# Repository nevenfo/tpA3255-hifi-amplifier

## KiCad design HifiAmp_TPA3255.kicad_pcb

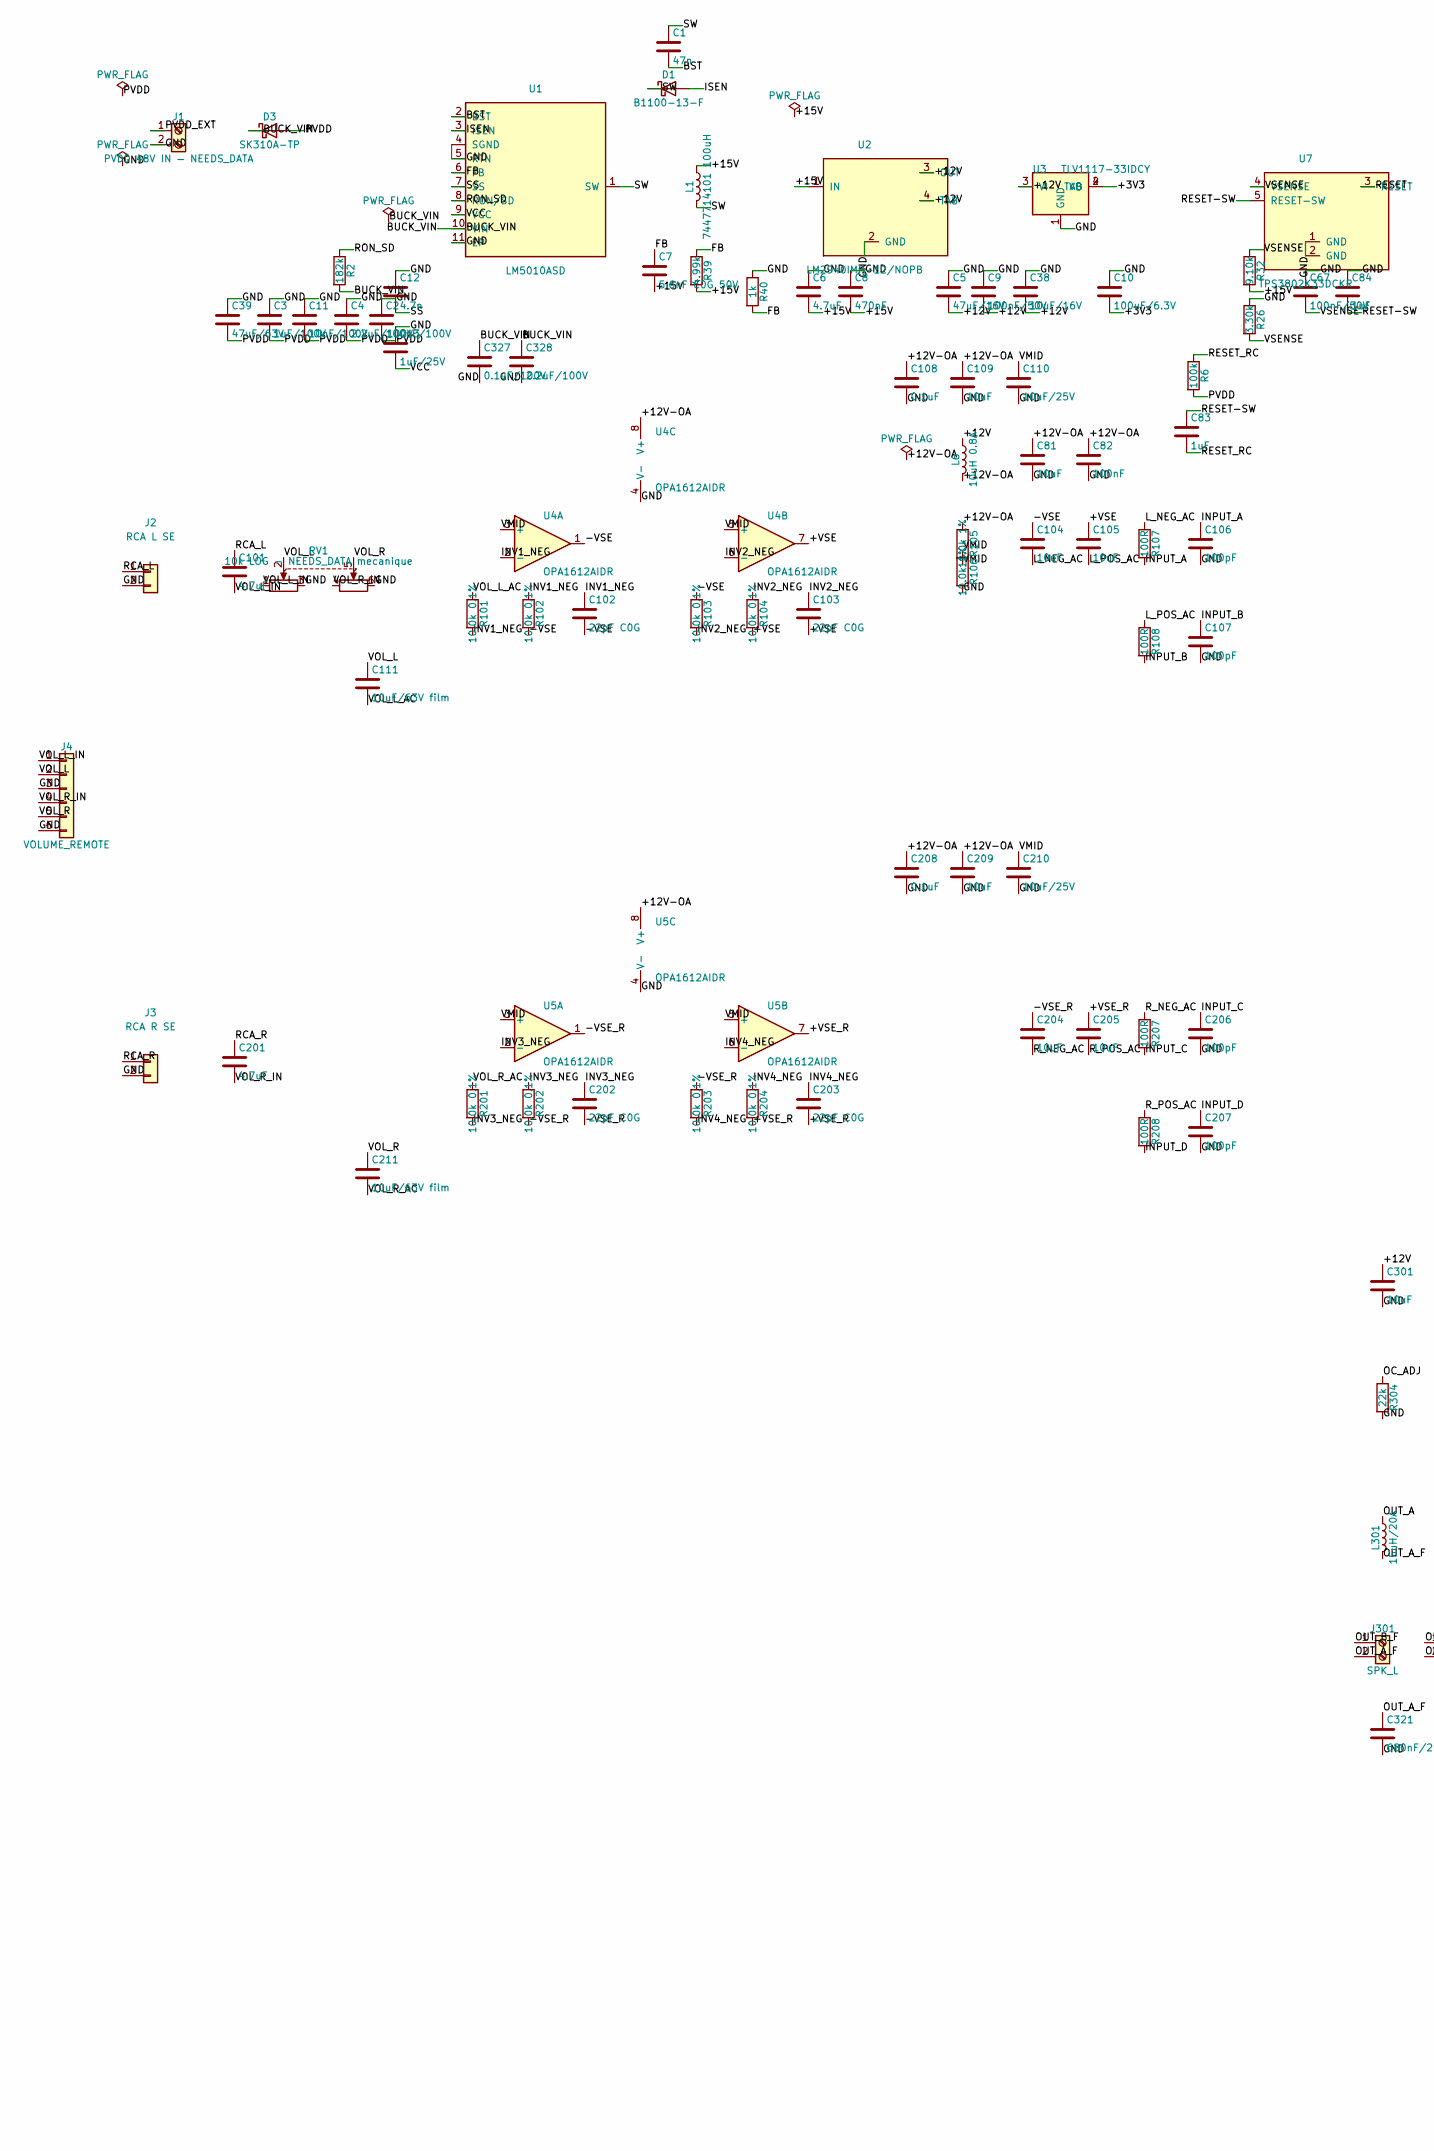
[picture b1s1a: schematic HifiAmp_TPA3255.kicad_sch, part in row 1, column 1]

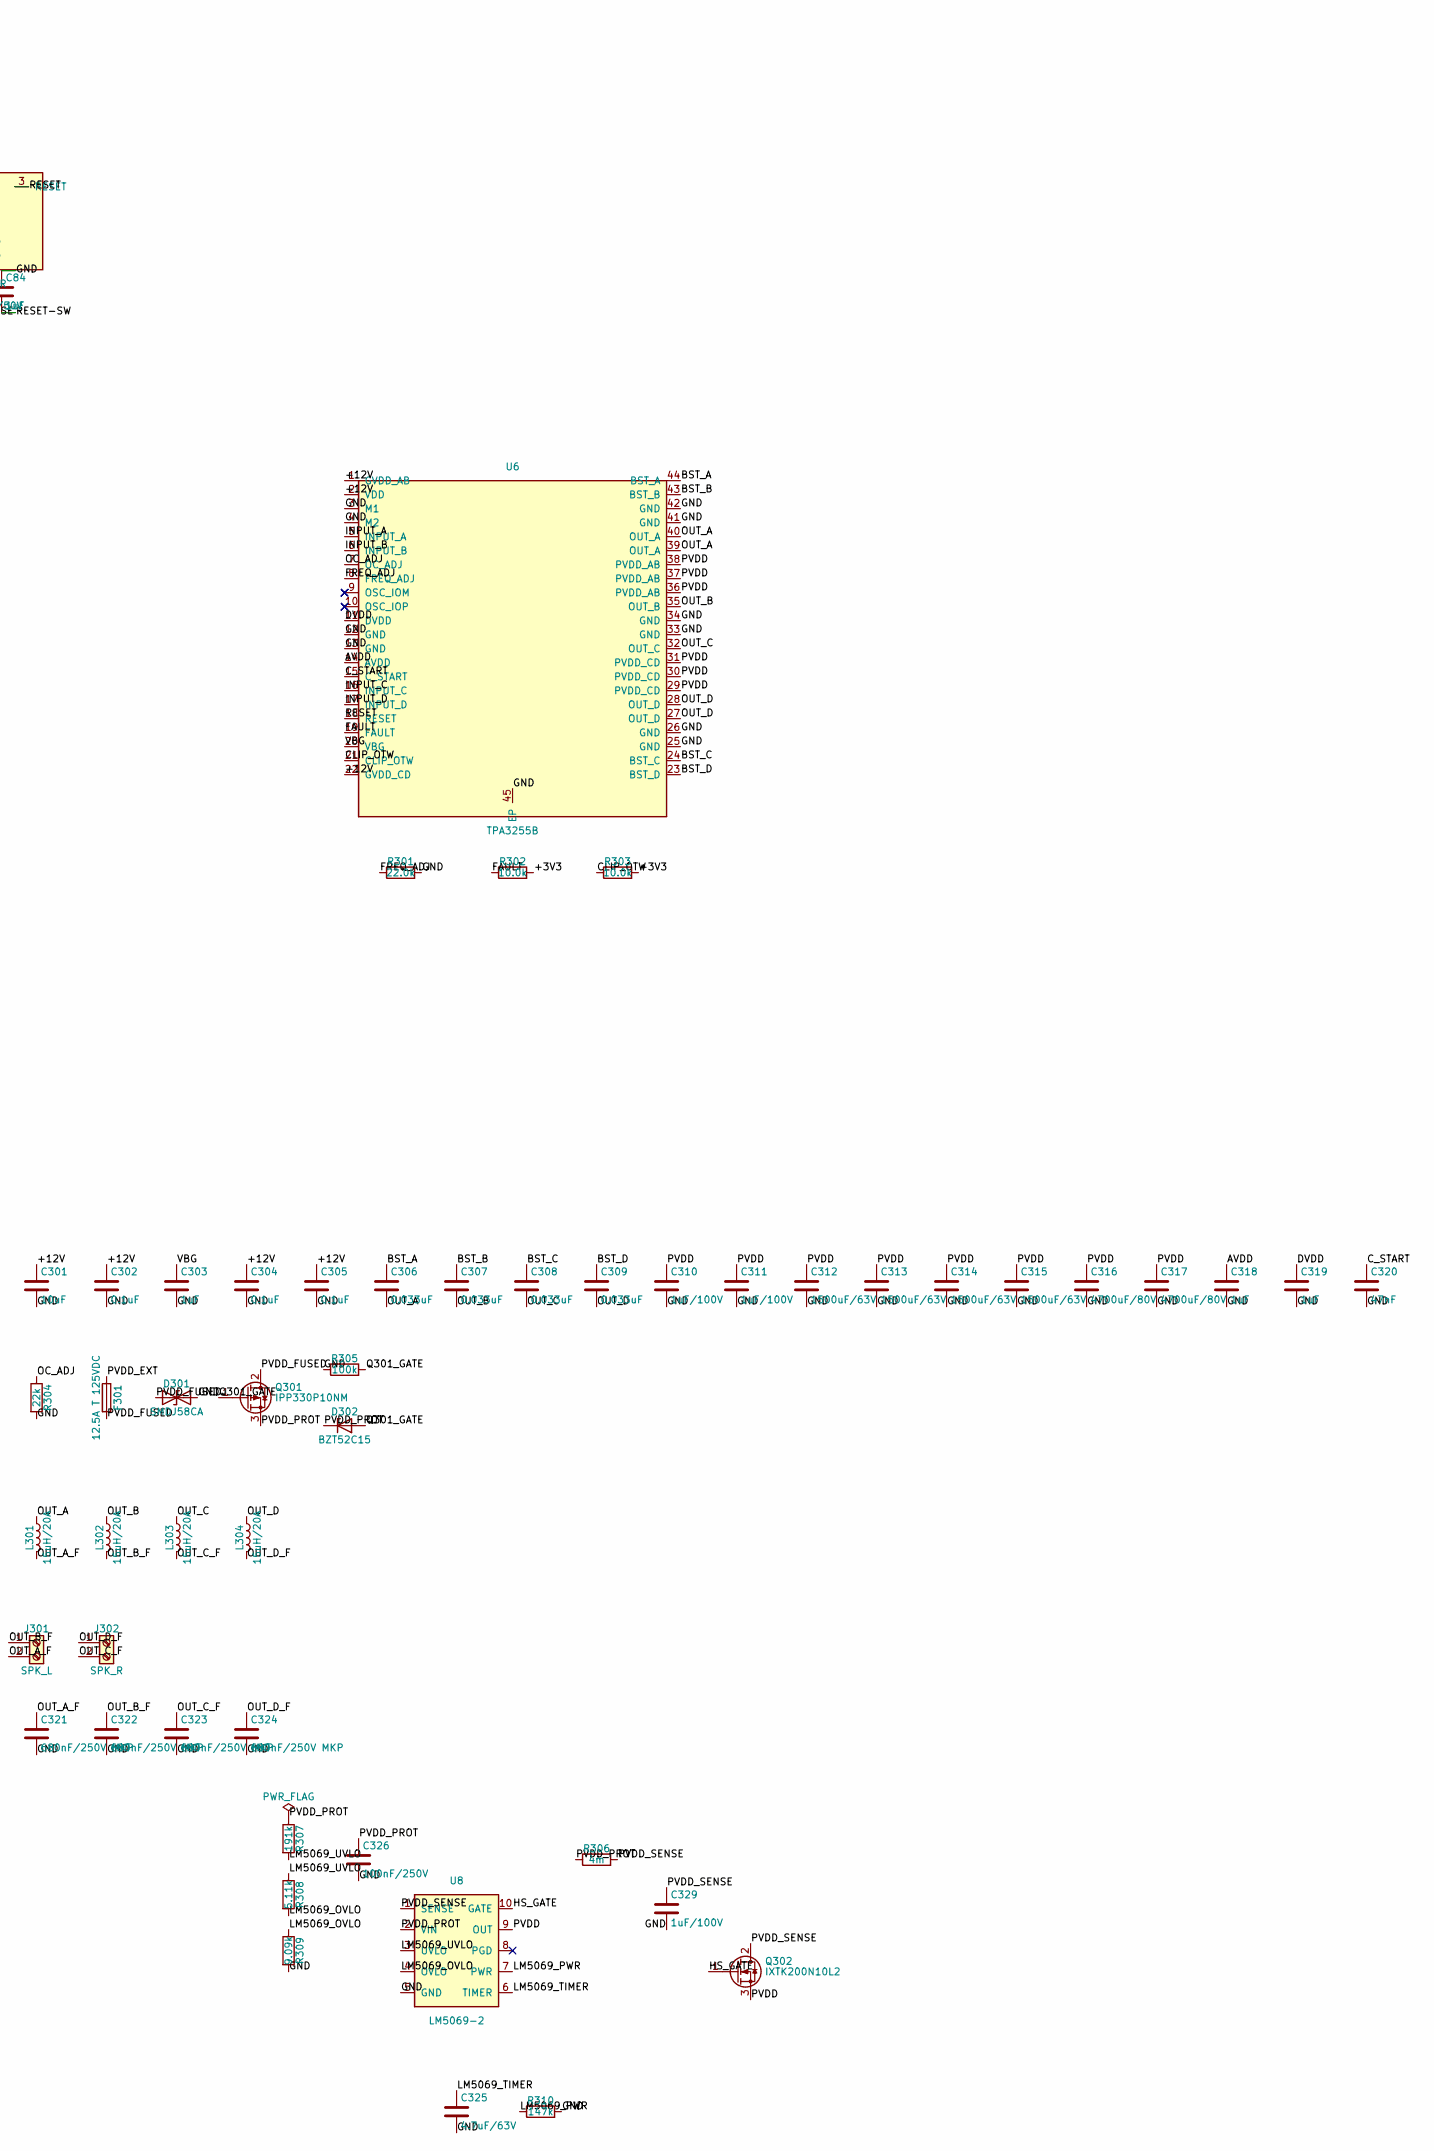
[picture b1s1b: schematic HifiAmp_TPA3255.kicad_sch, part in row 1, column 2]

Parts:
C1: 47n; C_0603_1608Metric
C2: 100nF/100V; C_1206_3216Metric
C3, C310, C311, C329: 1uF/100V; C_1210_3225Metric
C4: 2.2uF/100V; C_1812_4532Metric
C5: 47uF/16V; C_1210_3225Metric
C6, C101, C201: 4.7uF; C_0805_2012Metric
C7: 5.6nF C0G 50V; C_0603_1608Metric
C8: 470nF; C_0805_2012Metric
C9, C67: 100nF/50V; C_0805_2012Metric
C10: 100uF/6.3V; C_1210_3225Metric
C11: 10nF/100V; C_0805_2012Metric
C12: 4.7n; C_0603_1608Metric
C13: 1uF/25V; C_0603_1608Metric
C38: 10uF/16V; C_0805_2012Metric
C39: 47uF/63V; CP_Radial_D8.0mm_P3.50mm
C81, C104, C105, C109, C204, C205, C209, C301: 10uF; C_0805_2012Metric
C82: 100nF; C_0805_2012Metric
C83, C84, C303, C318, C319: 1uF; C_0805_2012Metric
C102, C103, C202, C203: 22pF C0G; C_0603_1608Metric
C106, C107, C206, C207: 100pF; C_0603_1608Metric
C108, C208, C302, C304, C305: 0.1uF; C_0603_1608Metric
C110, C210: 10uF/25V; C_0805_2012Metric
C111, C211: 10uF/63V film; C_Rect_L26.5mm_W10.5mm_P22.50mm_MKS4
C306, C307, C308, C309: 0.033uF; C_0603_1608Metric
C312, C313, C314, C315: 1500uF/63V; CP_Radial_D18.0mm_P7.50mm
C316, C317: 4700uF/80V; CP_Radial_D35.0mm_P10.00mm_SnapIn
C320: 47nF; C_0603_1608Metric
C321, C322, C323, C324: 680nF/250V MKP; C_Rect_L18.0mm_W8.0mm_P15.00mm_FKS3_FKP3
C325: 4.7uF/63V; C_Rect_L7.2mm_W11.0mm_P5.00mm_FKS2_FKP2_MKS2_MKP2; MPN MKS2C044701O00KSSD
C326: 100nF/250V; C_1206_3216Metric
C327: 0.1uF/100V; C_0603_1608Metric
C328: 2.2uF/100V; C_1210_3225Metric
D1: B1100-13-F; D_SMA
D3: SK310A-TP; D_SMA
D301: SMDJ58CA; D_SMC; MPN SMDJ58CA
D302: BZT52C15; D_SOD-123; MPN BZT52C15
F301: 12.5A T 125VDC; Fuse_Schurter_UMT-H_5.3x16mm; MPN 3403.0285.11
J1: PVDD 48V IN — NEEDS_DATA; TerminalBlock_MaiXu_MX126-5.0-02P_1x02_P5.00mm
J2: RCA L SE; JST_XH_B2B-XH-A_1x02_P2.50mm_Vertical
J3: RCA R SE; JST_XH_B2B-XH-A_1x02_P2.50mm_Vertical
J4: VOLUME_REMOTE; JST_XH_B6B-XH-A_1x06_P2.50mm_Vertical
J301: SPK_L; TerminalBlock_MaiXu_MX126-5.0-02P_1x02_P5.00mm
J302: SPK_R; TerminalBlock_MaiXu_MX126-5.0-02P_1x02_P5.00mm
L1: 7447714101 100uH; L_Wuerth_WE-PD-1050_10x10x5mm
L6: 10uH 0.8A; L_Wuerth_WE-PD-Typ-M-Typ-S
L301, L302, L303, L304: 15uH/20A; L_Toroid_Vertical_L28.6mm_W12.3mm_P10.00mm_Coilcraft_PA6331
Q301: IPP330P10NM; TO-220-3_Vertical; MPN IPP330P10NM
Q302: IXTK200N10L2; TO-264-3_Vertical; MPN IXTK200N10L2
R2: 182k; R_0603_1608Metric
R6: 100k; R_0603_1608Metric
R26: 3.30k; R_0603_1608Metric
R32: 9.10k; R_0603_1608Metric
R39: 4.99k; R_0603_1608Metric
R40: 1k; R_0603_1608Metric
R101, R102, R103, R104, R201, R202, R203, R204: 10.0k 0.1%; R_0603_1608Metric
R105, R106: 10.0k 1%; R_0603_1608Metric
R107, R108, R207, R208: 100R; R_0805_2012Metric
R301: 22.0k; R_0603_1608Metric
R302, R303: 10.0k; R_0603_1608Metric
R304: 22k; R_0603_1608Metric
R305: 100k; R_0805_2012Metric
R306: 4m; R_2512_6332Metric; MPN WSL25124L000FEA
R307: 191k; R_0805_2012Metric
R308: 5.11k; R_0603_1608Metric
R309: 9.09k; R_0603_1608Metric
R310: 147k; R_0603_1608Metric
RV1: 10k LOG - NEEDS_DATA mecanique
U1: LM5010ASD; WSON-10-1EP_4x4mm_P0.8mm_EP2.6x3mm
U2: LM2940IMP-12/NOPB; SOT-223
U3: TLV1117-33IDCY; SOT-223
U4, U5: OPA1612AIDR; SOIC-8_3.9x4.9mm_P1.27mm
U6: TPA3255B; HTSSOP-44_6.1x14mm_P0.635mm_TopEP4.14x7.01mm
U7: TPS3802K33DCKR; SOT-353_SC-70-5
U8: LM5069-2; MSOP-10_3x3mm_P0.5mm

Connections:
/+3V3: C10.2, R302.2, R303.2, U3.2 (VO), U3.4 (TAB)
/+12V: C5.2, C9.2, C38.2, C301.1, C302.1, C304.1, C305.1, L6.1, U2.3 (OUT), U2.4 (TAB), U3.3 (VI), U6.1 (GVDD_AB), U6.2 (VDD), U6.22 (GVDD_CD)
/+12V-OA: C81.1, C82.1, C108.1, C109.1, C208.1, C209.1, L6.2, R105.1, U4.8 (V+), U5.8 (V+)
/+15V: C6.2, C7.2, C8.2, L1.1, R32.2, R39.2, U2.1 (IN)
/+VSE: C103.2, C105.1, R104.2, U4.7
/+VSE_R: C203.2, C205.1, R204.2, U5.7
/-VSE: C102.2, C104.1, R102.2, R103.1, U4.1
/-VSE_R: C202.2, C204.1, R202.2, R203.1, U5.1
/AVDD: C318.1, U6.14 (AVDD)
/BST: C1.2, U1.2 (BST)
/BST_A: C306.1, U6.44 (BST_A)
/BST_B: C307.1, U6.43 (BST_B)
/BST_C: C308.1, U6.24 (BST_C)
/BST_D: C309.1, U6.23 (BST_D)
/BUCK_VIN: C327.1, C328.1, D3.1 (K), R2.2, U1.10 (VIN)
/CLIP_OTW: R303.1, U6.21 (CLIP_OTW)
/C_START: C320.1, U6.15 (C_START)
/DVDD: C319.1, U6.11 (DVDD)
/FAULT: R302.1, U6.19 (FAULT)
/FB: C7.1, R39.1, R40.2, U1.6 (FB)
/FREQ_ADJ: R301.1, U6.8 (FREQ_ADJ)
/GND: C2.1, C3.1, C4.1, C5.1, C6.1, C8.1, C9.1, C10.1, C11.1, C12.1, C13.1, C38.1, C39.1, C67.1, C81.2, C82.2, C84.1, C106.2, C107.2, C108.2, C109.2, C110.2, C206.2, C207.2, C208.2, C209.2, C210.2, C301.2, C302.2, C303.2, C304.2, C305.2, C310.2, C311.2, C312.2, C313.2, C314.2, C315.2, C316.2, C317.2, C318.2, C319.2, C320.2, C321.2, C322.2, C323.2, C324.2, C325.2, C326.2, C327.2, C328.2, C329.2, D301.2 (A2), J1.2, J2.2, J3.2, J4.3, J4.6, R26.1, R40.1, R106.2, R301.2, R304.2, R305.1, R309.2, R310.2, RV1.3, RV1.6, U1.4 (SGND), U1.5 (RTN), U1.11 (EP), U2.2 (GND), U3.1 (GND), U4.4 (V-), U5.4 (V-), U6.3 (M1), U6.4 (M2), U6.12 (GND), U6.13 (GND), U6.25 (GND), U6.26 (GND), U6.33 (GND), U6.34 (GND), U6.41 (GND), U6.42 (GND), U6.45 (EP), U7.1 (GND), U7.2 (GND), U8.5 (GND); also elsewhere on the board
/HS_GATE: Q302.1 (G), U8.10 (GATE)
/INPUT_A: C106.1, R107.2, U6.5 (INPUT_A)
/INPUT_B: C107.1, R108.2, U6.6 (INPUT_B)
/INPUT_C: C206.1, R207.2, U6.16 (INPUT_C)
/INPUT_D: C207.1, R208.2, U6.17 (INPUT_D)
/INV1_NEG: C102.1, R101.2, R102.1, U4.2 (-)
/INV2_NEG: C103.1, R103.2, R104.1, U4.6 (-)
/INV3_NEG: C202.1, R201.2, R202.1, U5.2 (-)
/INV4_NEG: C203.1, R203.2, R204.1, U5.6 (-)
/ISEN: D1.2 (A), U1.3 (ISEN)
/LM5069_OVLO: R308.2, R309.1, U8.4 (OVLO)
/LM5069_PWR: R310.1, U8.7 (PWR)
/LM5069_TIMER: C325.1, U8.6 (TIMER)
/LM5069_UVLO: R307.2, R308.1, U8.3 (UVLO)
/L_NEG_AC: C104.2, R107.1
/L_POS_AC: C105.2, R108.1
/OC_ADJ: R304.1, U6.7 (OC_ADJ)
/OUT_A: C306.2, L301.1, U6.39 (OUT_A), U6.40 (OUT_A)
/OUT_A_F: C321.1, J301.2, L301.2; also elsewhere on the board
/OUT_B: C307.2, L302.1, U6.35 (OUT_B)
/OUT_B_F: C322.1, J301.1, L302.2; also elsewhere on the board
/OUT_C: C308.2, L303.1, U6.32 (OUT_C)
/OUT_C_F: C323.1, J302.2, L303.2; also elsewhere on the board
/OUT_D: C309.2, L304.1, U6.27 (OUT_D), U6.28 (OUT_D)
/OUT_D_F: C324.1, J302.1, L304.2; also elsewhere on the board
/PVDD: C2.2, C3.2, C4.2, C11.2, C39.2, C310.1, C311.1, C312.1, C313.1, C314.1, C315.1, C316.1, C317.1, D3.2 (A), Q302.3 (S), R6.2, U6.29 (PVDD_CD), U6.30 (PVDD_CD), U6.31 (PVDD_CD), U6.36 (PVDD_AB), U6.37 (PVDD_AB), U6.38 (PVDD_AB), U8.9 (OUT)
/PVDD_EXT: F301.1, J1.1
/PVDD_FUSED: D301.1 (A1), F301.2, Q301.2 (D)
/PVDD_PROT: C326.1, D302.1 (K), Q301.3 (S), R306.1, R307.1, U8.2 (VIN)
/PVDD_SENSE: C329.1, Q302.2 (D), R306.2, U8.1 (SENSE)
/Q301_GATE: D302.2 (A), Q301.1 (G), R305.2
/RCA_L: C101.1, J2.1
/RCA_R: C201.1, J3.1
/RESET: U6.18 (RESET), U7.3 (RESET)
/RESET-SW: C83.1, C84.2, U7.5 (RESET-SW)
/RESET_RC: C83.2, R6.1
/RON_SD: R2.1, U1.8 (RON/SD)
/R_NEG_AC: C204.2, R207.1
/R_POS_AC: C205.2, R208.1
/SS: C12.2, U1.7 (SS)
/SW: C1.1, D1.1 (K), L1.2, U1.1 (SW)
/VBG: C303.1, U6.20 (VBG)
/VCC: C13.2, U1.9 (VCC)
/VMID: C110.1, C210.1, R105.2, R106.1, U4.3 (+), U4.5 (+), U5.3 (+), U5.5 (+)
/VOL_L: C111.1, J4.2, RV1.2
/VOL_L_AC: C111.2, R101.1
/VOL_L_IN: C101.2, J4.1, RV1.1
/VOL_R: C211.1, J4.5, RV1.5
/VOL_R_AC: C211.2, R201.1
/VOL_R_IN: C201.2, J4.4, RV1.4
/VSENSE: C67.2, R26.2, R32.1, U7.4 (VSENSE)

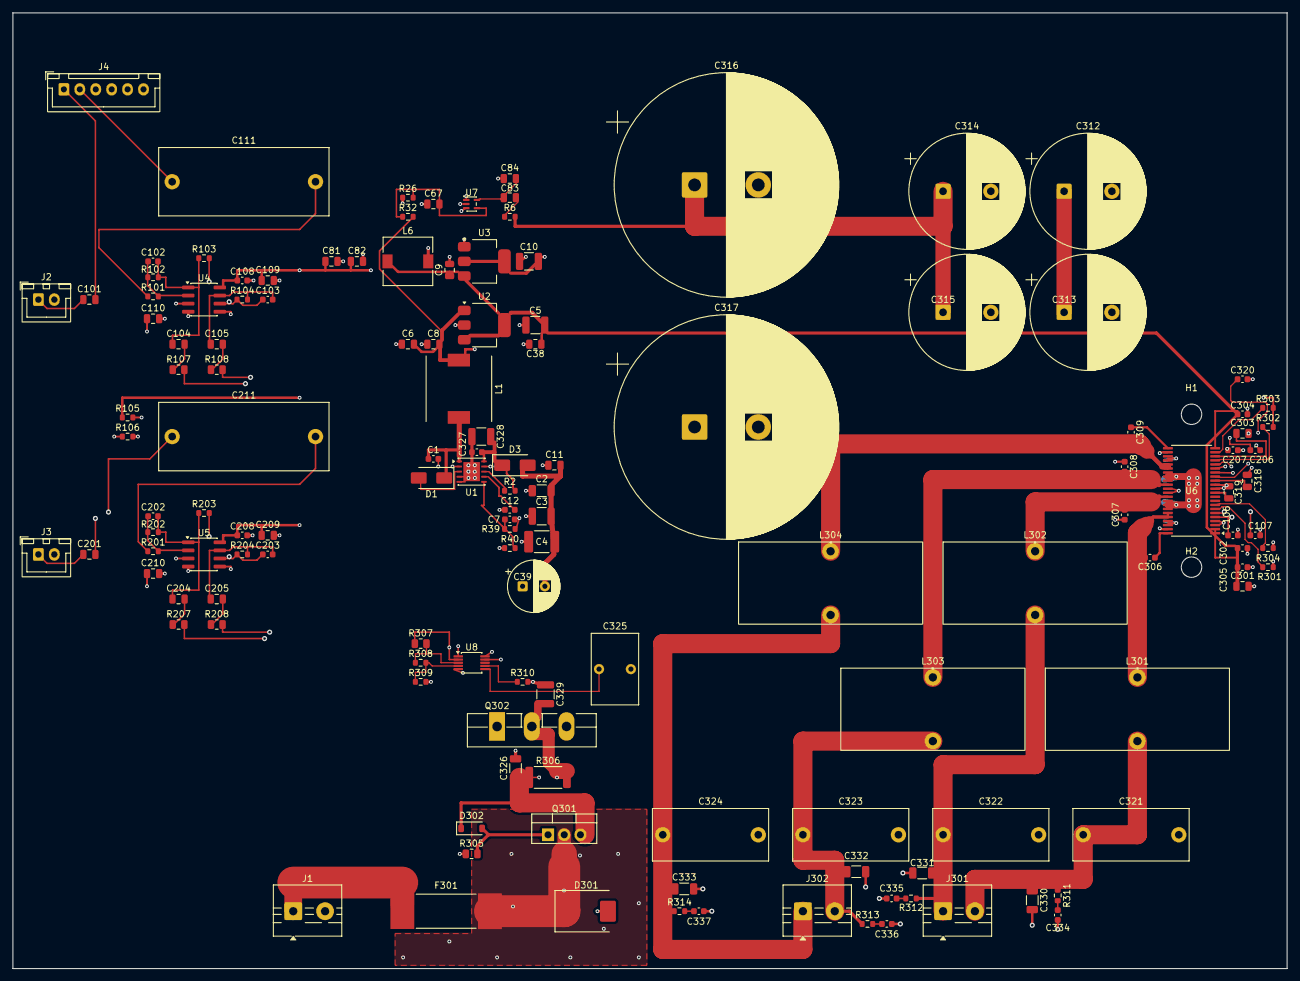
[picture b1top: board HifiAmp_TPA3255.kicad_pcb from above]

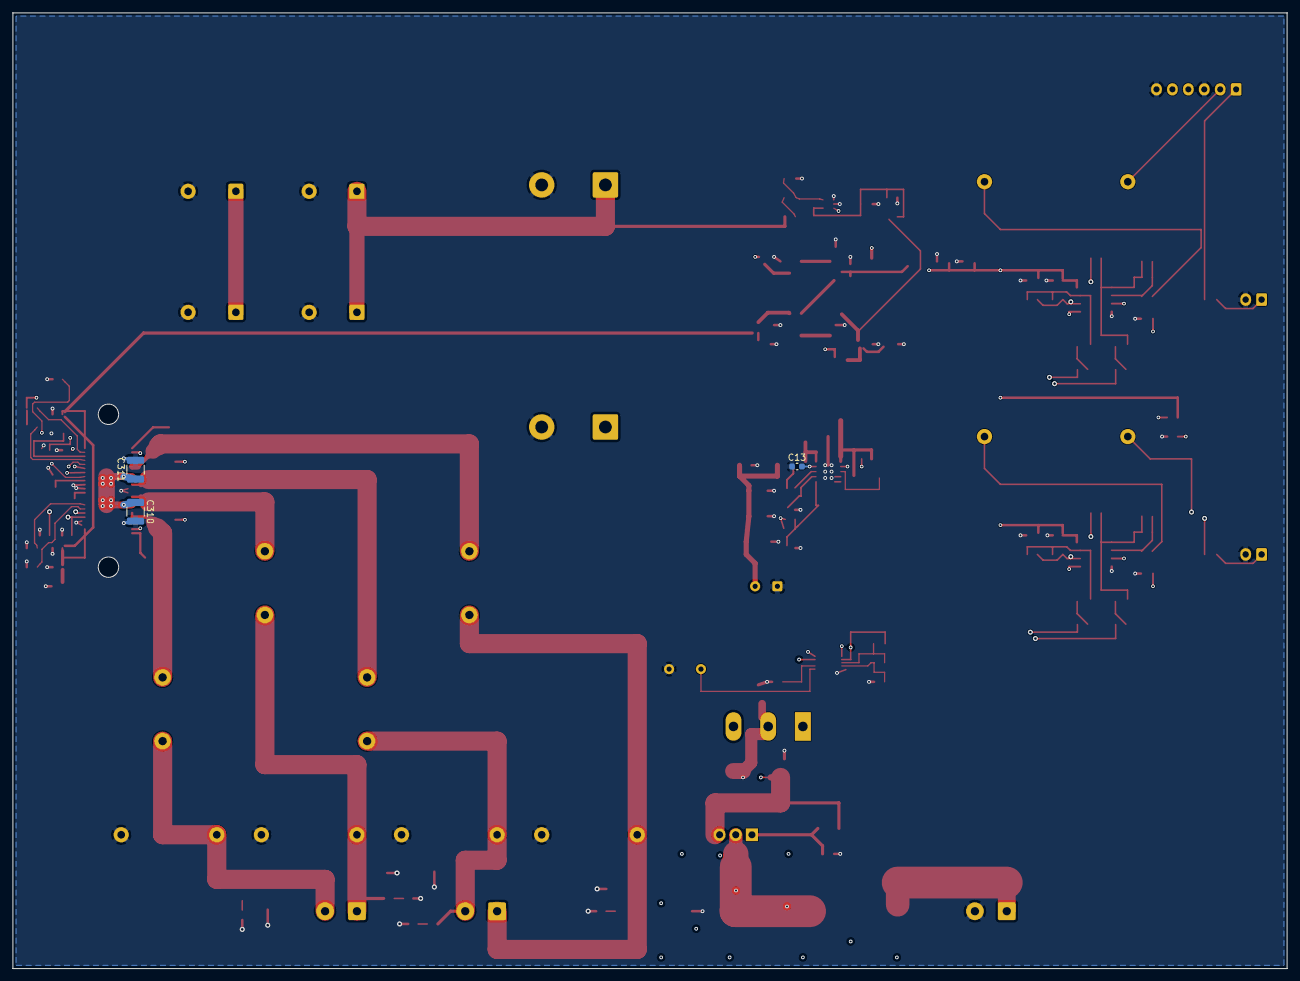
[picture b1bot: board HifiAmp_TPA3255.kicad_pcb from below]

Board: 4 copper layers, 200.0 x 150.0 mm, 142 parts (3 on the bottom side), 77 nets.

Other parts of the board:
C330, C331, C332, C333: 1nF/100V C0G; C_1206_3216Metric
C334, C335, C336, C337: 10nF/100V X7R; C_0603_1608Metric
H1, H2: MountingHole_3.2mm_M3
R311, R312, R313, R314: 3R3 0.1W; R_0603_1608Metric

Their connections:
/GND: C330.2, C331.2, C332.2, C333.2, C334.2, C335.2, C336.2, C337.2; also elsewhere on the board
/OUT_A_F: C330.1, R311.1; also elsewhere on the board
/OUT_B_F: C331.1, R312.1; also elsewhere on the board
/OUT_C_F: C332.1, R313.1; also elsewhere on the board
/OUT_D_F: C333.1, R314.1; also elsewhere on the board
/SNUB_A: C334.1, R311.2
/SNUB_B: C335.1, R312.2
/SNUB_C: C336.1, R313.2
/SNUB_D: C337.1, R314.2
